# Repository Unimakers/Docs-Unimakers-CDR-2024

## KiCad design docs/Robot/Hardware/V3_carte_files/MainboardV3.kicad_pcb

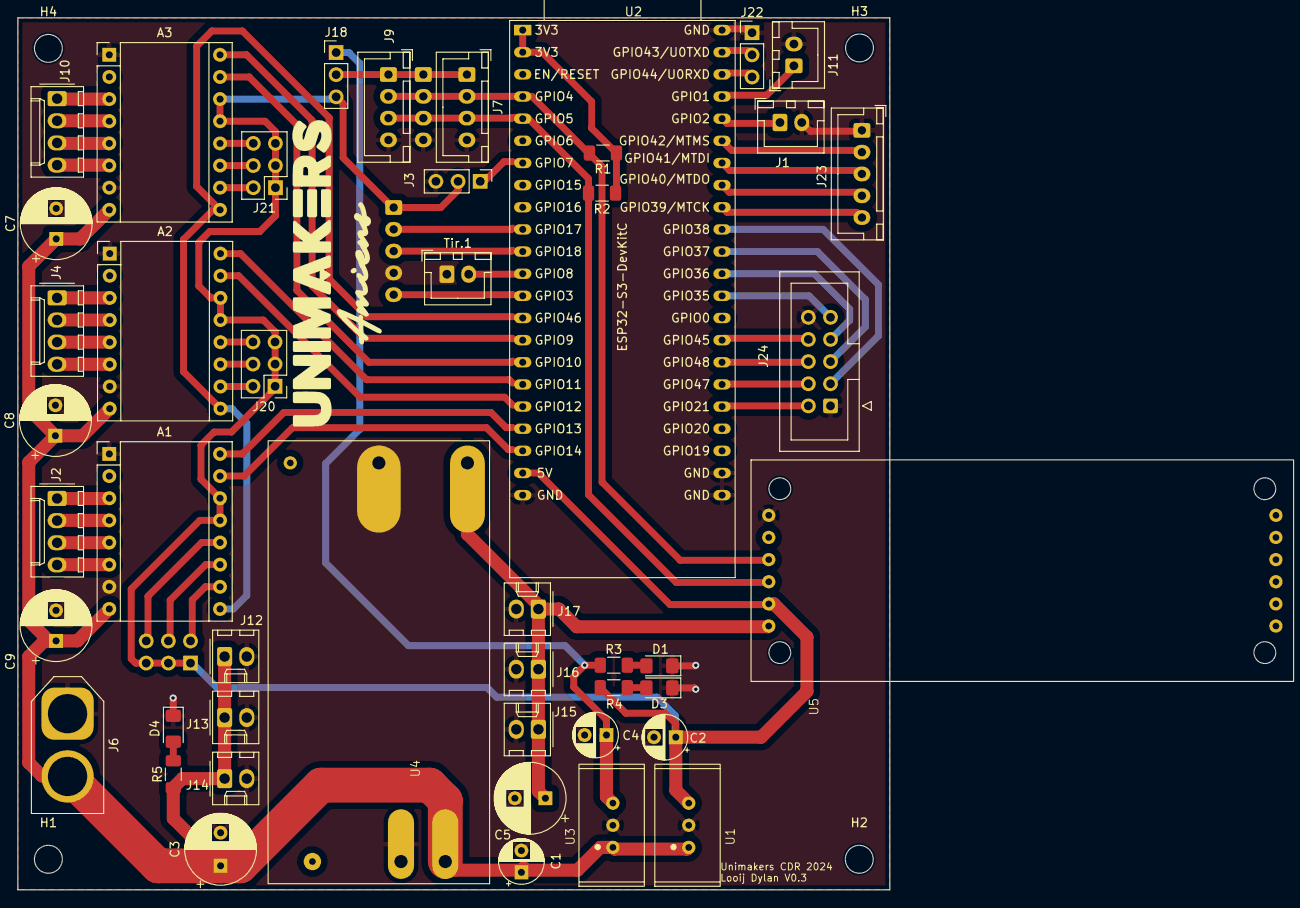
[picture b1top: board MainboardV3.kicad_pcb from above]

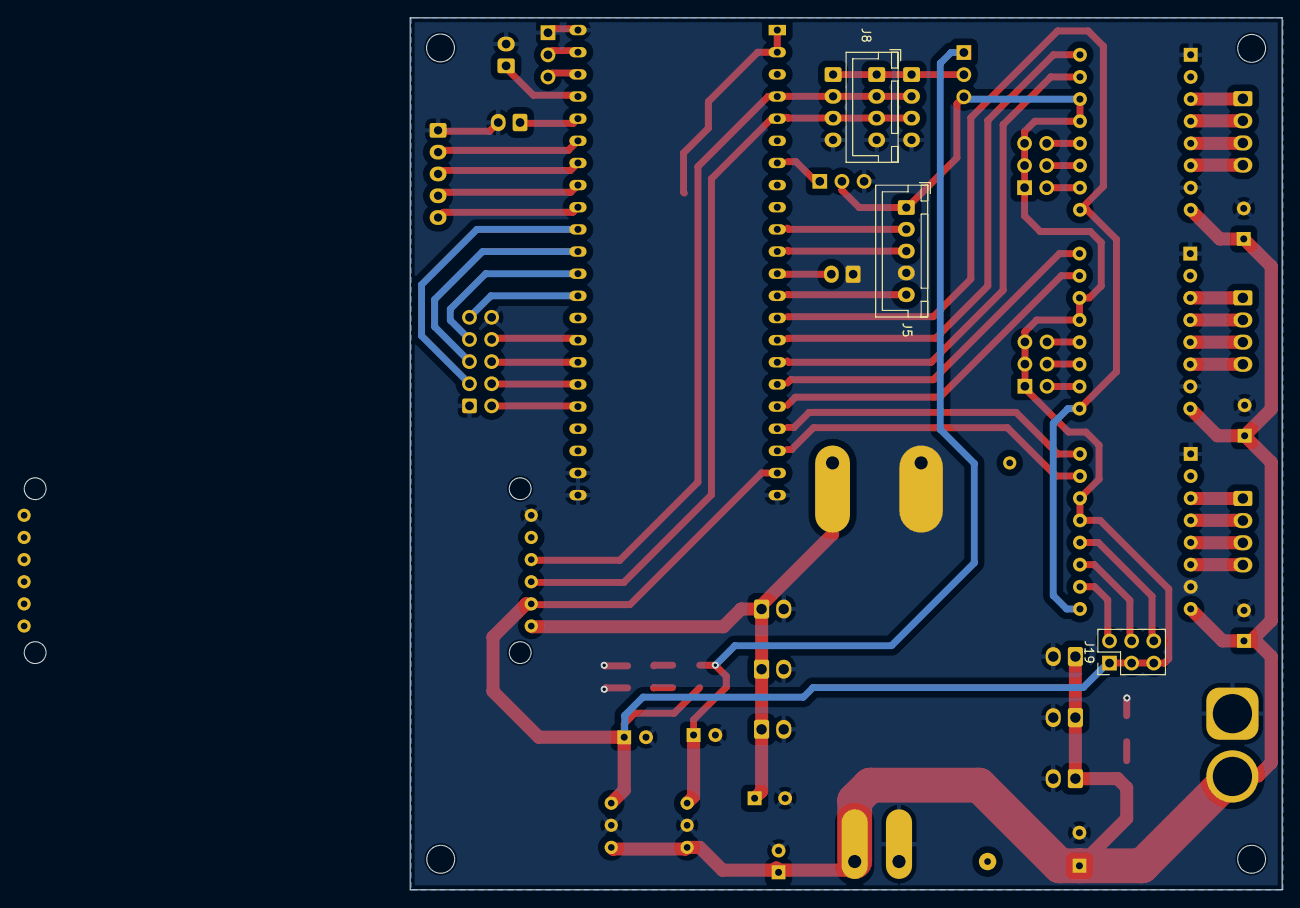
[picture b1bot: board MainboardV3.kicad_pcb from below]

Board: 2 copper layers, 100.0 x 100.0 mm, 53 parts (3 on the bottom side), 61 nets.

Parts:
A1, A2, A3: Pololu_Breakout_DRV8825; Pololu_Breakout-16_15.2x20.3mm
C1, C2, C4: C_Polarized; CP_Radial_D5.0mm_P2.50mm
C3: C_Polarized; CP_Radial_D8.0mm_P3.80mm
C5, C7, C8, C9: C_Polarized; CP_Radial_D8.0mm_P3.50mm
D1, D3, D4: LED_Small; LED_1206_3216Metric_Pad1.42x1.75mm_HandSolder
H1, H2, H3, H4: MountingHole; MountingHole_3.2mm_M3
J1, J11: Conn_01x02; JST_XH_B2B-XH-A_1x02_P2.50mm_Vertical
J2, J4, J10: Conn_01x04; Molex_KK-254_AE-6410-04A_1x04_P2.54mm_Vertical
J3, J18, J22: Conn_01x03; PinHeader_1x03_P2.54mm_Vertical
J5, J23: Conn_01x05; JST_XH_B5B-XH-A_1x05_P2.50mm_Vertical
J6: Conn_01x02; AMASS_XT60-M_1x02_P7.20mm_Vertical
J7, J8, J9: Conn_01x04; JST_XH_B4B-XH-A_1x04_P2.50mm_Vertical
J12, J13, J14, J15, J16, J17: Conn_01x02; Molex_KK-254_AE-6410-02A_1x02_P2.54mm_Vertical
J19, J20, J21: Conn_02x03_Odd_Even; PinHeader_2x03_P2.54mm_Vertical
J24: Conn_02x05_Odd_Even; IDC-Header_2x05_P2.54mm_Vertical
R1, R2: R; R_1206_3216Metric_Pad1.30x1.75mm_HandSolder
R3, R4, R5: R_Small; R_1206_3216Metric_Pad1.30x1.75mm_HandSolder
Tir.1: Conn_01x02; JST_XH_B2B-XH-A_1x02_P2.50mm_Vertical
U1: TSR_2-2450; Traco 2- 24xx
U2: ESP32-S3-DevKitC
U3: TSR_2-2433; Traco 2- 24xx
U4: TEN_50-2411WI; Traco TEN 50 series
U5: PCA9685breakout

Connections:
+3.3V: R1.1, R2.1, U2.1 (3V3), U2.2 (3V3)
+3.3VP: C4.1, J18.1, R3.1, U3.3 (VO)
+5V: A1.13 (~RST), A1.14 (~SLP), A2.13 (~RST), A2.14 (~SLP), A3.13 (~RST), A3.14 (~SLP), C2.1, J3.2, J5.1, J18.3, J19.1, J19.3, J19.5, J20.1, J20.3, J20.5, J21.1, J21.3, J21.5, R4.1, U1.3 (VO), U2.21 (5V), U5.4 (VCC)
+5VP: C5.1, J15.1, J16.1, J17.1, U4.4 (+Vout), U5.5 (V+_6VMax)
+12V: A1.8 (VMOT), A2.8 (VMOT), A3.8 (VMOT), C1.1, C3.1, C7.1, C8.1, C9.1, J6.2, J12.1, J13.1, J14.1, R5.1, U1.1 (VI), U3.1 (VI), U4.1 (+Vin)
/GP1: J11.1, U2.41 (GPIO1/ADC1_CH0)
/GP2: J1.1, U2.40 (GPIO2/ADC1_CH1)
DIR1: A1.16 (DIR), U2.19 (GPIO13/ADC2_CH2)
DIR2: A2.16 (DIR), U2.17 (GPIO11/ADC2_CH0)
DIR3: A3.16 (DIR), U2.15 (GPIO9/ADC1_CH8)
EN: A1.9 (~EN), A2.9 (~EN), A3.9 (~EN), U2.14 (GPIO46)
GND: A1.1 (GND), A1.7 (GND), A2.1 (GND), A2.7 (GND), A3.1 (GND), A3.7 (GND), C1.2, C2.2, C3.2, C4.2, C5.2, C7.2, C8.2, C9.2, D1.1 (K), D3.1 (K), D4.1 (K), J1.2, J3.3, J5.4, J6.1, J7.4, J8.4, J9.4, J11.2, J12.2, J13.2, J14.2, J15.2, J16.2, J17.2, J22.1, J23.1, J24.1, J24.10, Tir.1.1, U1.2 (GND), U2.22 (GND), U2.23 (GND), U2.24 (GND), U2.44 (GND), U3.2 (GND), U4.2 (-Vin), U4.5 (-Vout), U5.0 (GND)
GPI035: J24.9, U2.32 (GPIO35)
GPIO21: J24.2, U2.27 (GPIO21)
GPIO36: J24.7, U2.33 (GPIO36)
GPIO37: J24.5, U2.34 (GPIO37)
GPIO38: J24.3, U2.35 (GPIO38)
GPIO45: J24.8, U2.30 (GPIO45)
GPIO47: J24.4, U2.28 (GPIO47)
GPIO48: J24.6, U2.29 (GPIO48)
LIDARRX: J5.2, U2.10 (GPIO17/ADC2_CH6)
LIDARTX: J5.3, U2.11 (GPIO18/ADC2_CH7)
Neopixel: J3.1, U2.7 (GPIO7/ADC1_CH6)
unnamed: A1.4 (A1), J2.2
unnamed: A1.3 (A2), J2.1
unnamed: A1.5 (B1), J2.3
unnamed: A1.6 (B2), J2.4
unnamed: A1.10 (M0), J19.2
unnamed: A1.11 (M1), J19.4
unnamed: A1.12 (M2), J19.6
unnamed: A2.4 (A1), J4.2
unnamed: A2.3 (A2), J4.1
unnamed: A2.5 (B1), J4.3
unnamed: A2.6 (B2), J4.4
unnamed: A2.10 (M0), J20.2
unnamed: A2.11 (M1), J20.4
unnamed: A2.12 (M2), J20.6
unnamed: A3.4 (A1), J10.2
unnamed: A3.3 (A2), J10.1
unnamed: A3.5 (B1), J10.3
unnamed: A3.6 (B2), J10.4
unnamed: A3.10 (M0), J21.2
unnamed: A3.11 (M1), J21.4
unnamed: A3.12 (M2), J21.6
unnamed: D1.2 (A), R3.2
unnamed: D3.2 (A), R4.2
unnamed: D4.2 (A), R5.2
unnamed: J7.1, J8.1, J9.1, J18.2
unnamed: J22.2, U2.43 (GPIO43/U0TXD)
unnamed: J22.3, U2.42 (GPIO44/U0RXD)
unnamed: J23.2, U2.39 (GPIO42/MTMS)
unnamed: J23.3, U2.38 (GPIO41/MTDI)
unnamed: J23.4, U2.37 (GPIO40/MTDO)
unnamed: J23.5, U2.36 (GPIO39/MTCK)
unnamed: Tir.1.2, U2.12 (GPIO8/ADC1_CH7)
PWMLIDAR: J5.5, U2.13 (GPIO3/ADC1_CH2)
SCL: J7.2, J8.2, J9.2, R1.2, U2.4 (GPIO4/ADC1_CH3), U5.2 (SCL)
SDA: J7.3, J8.3, J9.3, R2.2, U2.5 (GPIO5/ADC1_CH4), U5.3 (SDA)
STEP1: A1.15 (STEP), U2.20 (GPIO14/ADC2_CH3)
STEP2: A2.15 (STEP), U2.18 (GPIO12/ADC2_CH1)
STEP3: A3.15 (STEP), U2.16 (GPIO10/ADC1_CH9)

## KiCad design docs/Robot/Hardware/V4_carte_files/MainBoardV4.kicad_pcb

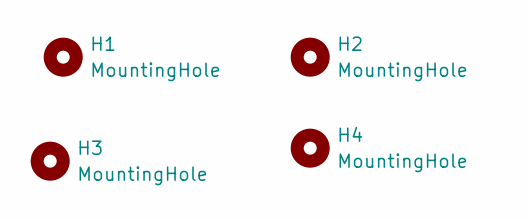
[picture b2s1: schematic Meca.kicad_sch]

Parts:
H1, H2, H3, H4: MountingHole; MountingHole_3.2mm_M3

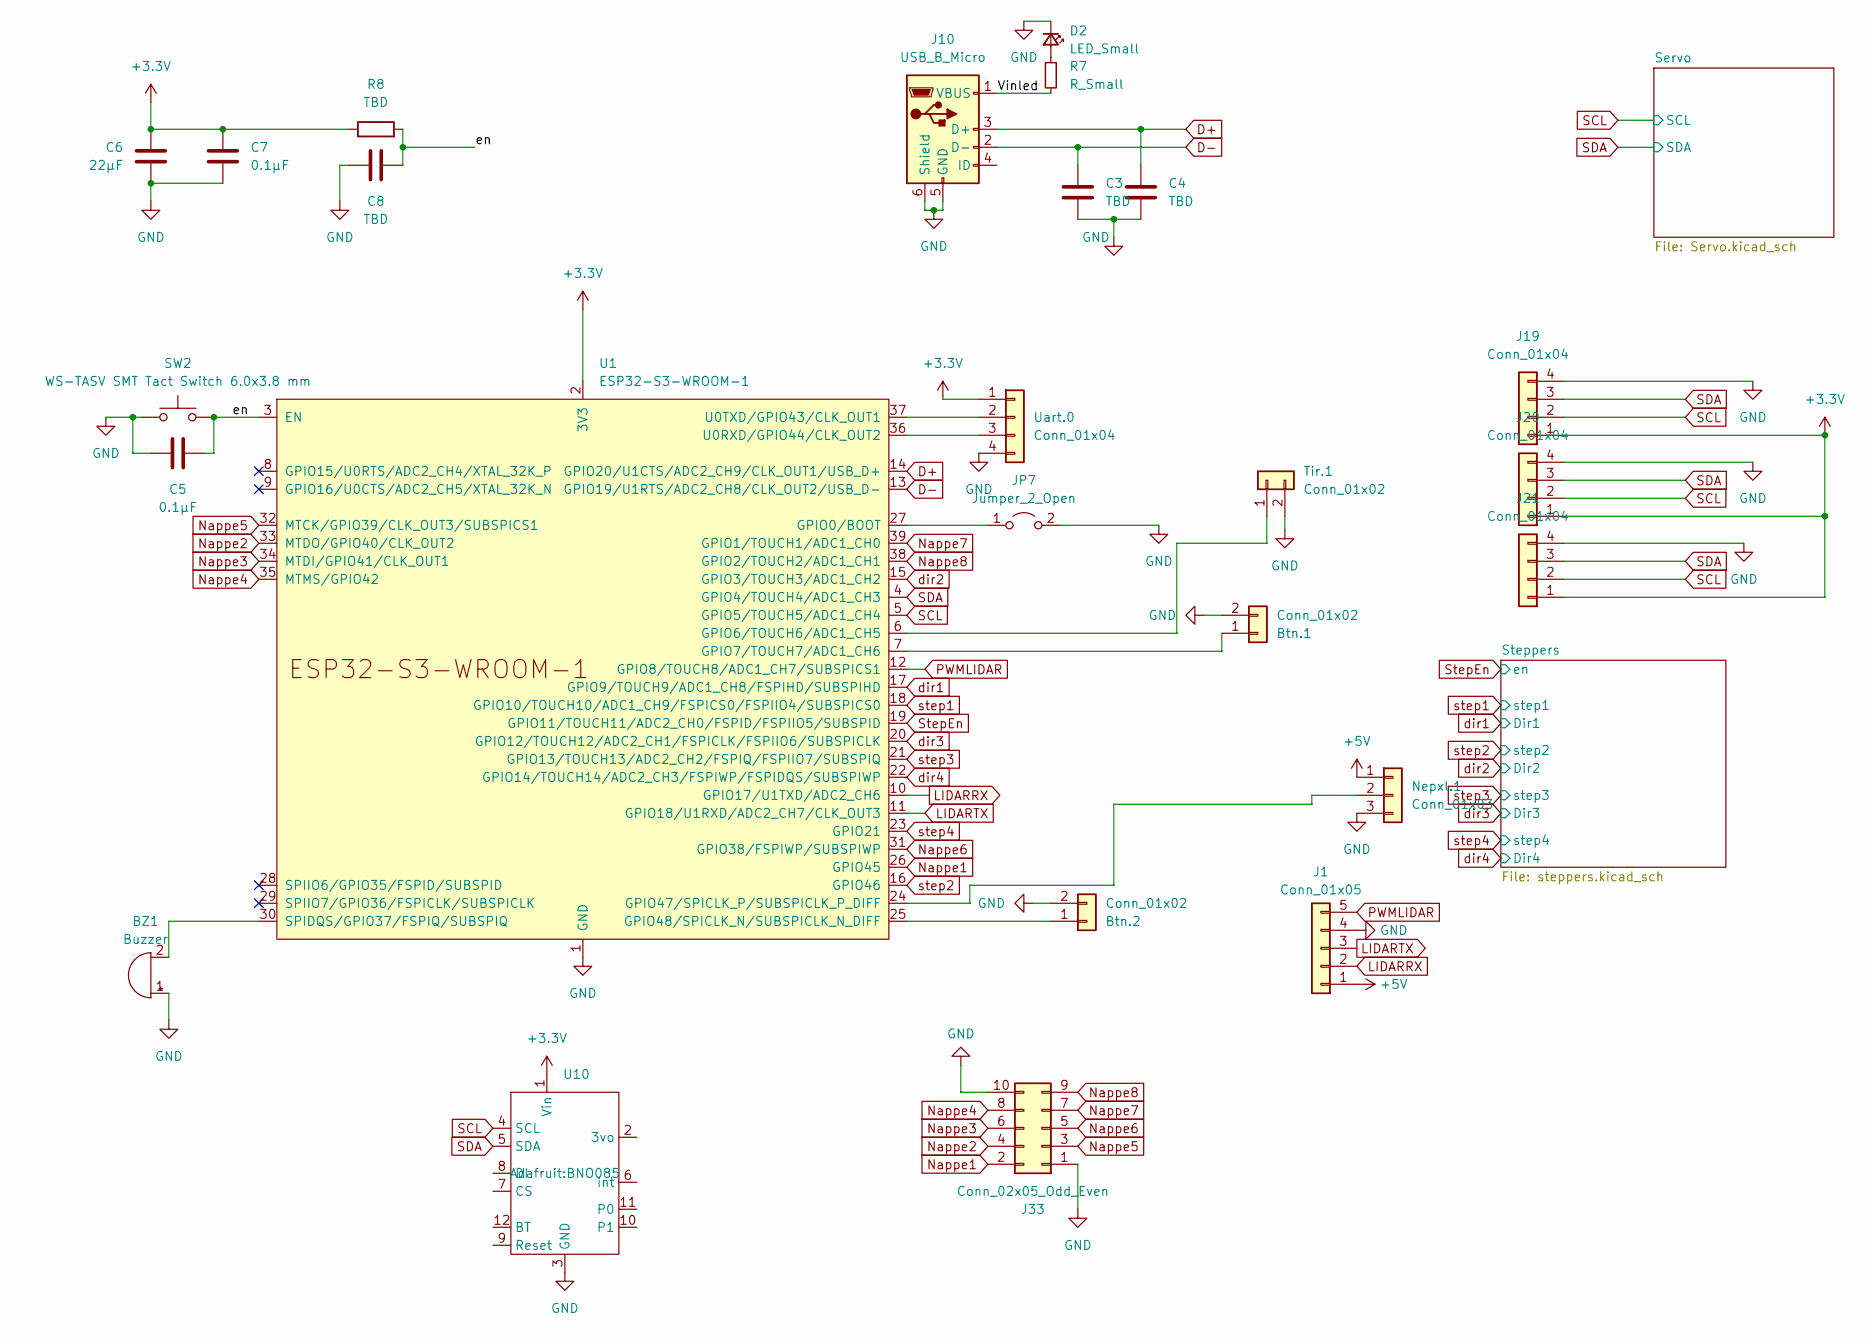
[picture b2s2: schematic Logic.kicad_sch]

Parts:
BZ1: Buzzer; Buzzer_12x9.5RM7.6
Btn.1, Btn.2: Conn_01x02; JST_XH_B2B-XH-A_1x02_P2.50mm_Vertical
C3, C4, C8: TBD; C_0805_2012Metric_Pad1.18x1.45mm_HandSolder
C5, C7: 0.1µF; C_0805_2012Metric_Pad1.18x1.45mm_HandSolder
C6: 22µF; C_0805_2012Metric_Pad1.18x1.45mm_HandSolder
D2: LED_Small; LED_1206_3216Metric_Pad1.42x1.75mm_HandSolder
J1: Conn_01x05; JST_XH_B5B-XH-A_1x05_P2.50mm_Vertical
J10: USB_B_Micro; USB_Micro-B_Wuerth_629105150521
J19, J20, J21: Conn_01x04; JST_XH_B4B-XH-A_1x04_P2.50mm_Vertical
J33: Conn_02x05_Odd_Even; IDC-Header_2x05_P2.54mm_Vertical
JP7: Jumper_2_Open; PinHeader_1x02_P2.54mm_Vertical
Nepxl.1: Conn_01x03; PinSocket_1x03_P2.54mm_Vertical
R7: R_Small; R_1206_3216Metric_Pad1.30x1.75mm_HandSolder
R8: TBD; R_1206_3216Metric_Pad1.30x1.75mm_HandSolder
SW2: WS-TASV SMT Tact Switch 6.0x3.8 mm; WS-TASV SMT Tact Switch
Tir.1: Conn_01x02; JST_XH_B2B-XH-A_1x02_P2.50mm_Vertical
U1: ESP32-S3-WROOM-1
U10: BNO085
Uart.0: Conn_01x04; JST_XH_B4B-XH-A_1x04_P2.50mm_Vertical

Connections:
+3.3V: C6.2, C7.2, J19.1, J20.1, J21.1, R8.1, U1.2 (3V3), U10.1 (Vin), Uart.0.1; also elsewhere on the board
+5V: J1.1, Nepxl.1.1; also elsewhere on the board
/Logic/Vinled: J10.1 (VBUS), R7.2
/Logic/en: C5.2, C8.1, R8.2, SW2.2, U1.3 (EN)
D+: C4.1, J10.3 (D+), U1.14 (GPIO20/U1CTS/ADC2_CH9/CLK_OUT1/USB_D+)
D-: C3.1, J10.2 (D-), U1.13 (GPIO19/U1RTS/ADC2_CH8/CLK_OUT2/USB_D-)
GND: BZ1.1 (-), Btn.1.2, Btn.2.2, C3.2, C4.2, C5.1, C6.1, C7.1, C8.2, D2.1 (K), J1.4, J10.5 (GND), J10.6 (Shield), J19.4, J20.4, J21.4, J33.1, J33.10, JP7.2 (B), Nepxl.1.3, SW2.1, Tir.1.2, U1.1 (GND), U1.40 (GND), U1.41 (GND), U10.3 (GND), Uart.0.4; also elsewhere on the board
LIDARRX: J1.2, U1.10 (GPIO17/U1TXD/ADC2_CH6)
LIDARTX: J1.3, U1.11 (GPIO18/U1RXD/ADC2_CH7/CLK_OUT3)
Nappe1: J33.2, U1.26 (GPIO45)
Nappe2: J33.4, U1.33 (MTDO/GPIO40/CLK_OUT2)
Nappe3: J33.6, U1.34 (MTDI/GPIO41/CLK_OUT1)
Nappe4: J33.8, U1.35 (MTMS/GPIO42)
Nappe5: J33.3, U1.32 (MTCK/GPIO39/CLK_OUT3/SUBSPICS1)
Nappe6: J33.5, U1.31 (GPIO38/FSPIWP/SUBSPIWP)
Nappe7: J33.7, U1.39 (GPIO1/TOUCH1/ADC1_CH0)
Nappe8: J33.9, U1.38 (GPIO2/TOUCH2/ADC1_CH1)
unnamed: BZ1.2 (+), U1.30 (SPIDQS/GPIO37/FSPIQ/SUBSPIQ)
unnamed: Btn.1.1, U1.7 (GPIO7/TOUCH7/ADC1_CH6)
unnamed: Btn.2.1, U1.25 (GPIO48/SPICLK_N/SUBSPICLK_N_DIFF)
unnamed: D2.2 (A), R7.1
unnamed: JP7.1 (A), U1.27 (GPIO0/BOOT)
unnamed: Nepxl.1.2, U1.24 (GPIO47/SPICLK_P/SUBSPICLK_P_DIFF)
unnamed: Tir.1.1, U1.6 (GPIO6/TOUCH6/ADC1_CH5)
unnamed: U1.36 (U0RXD/GPIO44/CLK_OUT2), Uart.0.3
unnamed: U1.37 (U0TXD/GPIO43/CLK_OUT1), Uart.0.2
PWMLIDAR: J1.5, U1.12 (GPIO8/TOUCH8/ADC1_CH7/SUBSPICS1)
SCL: J19.2, J20.2, J21.2, U1.5 (GPIO5/TOUCH5/ADC1_CH4), U10.4 (SCL); also elsewhere on the board
SDA: J19.3, J20.3, J21.3, U1.4 (GPIO4/TOUCH4/ADC1_CH3), U10.5 (SDA); also elsewhere on the board
StepEn: U1.19 (GPIO11/TOUCH11/ADC2_CH0/FSPID/FSPIIO5/S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); also elsewhere on the board
dir1: U1.17 (GPIO9/TOUCH9/ADC1_CH8/FSPIHD/SUBSPIHD); also elsewhere on the board
dir2: U1.15 (GPIO3/TOUCH3/ADC1_CH2); also elsewhere on the board
dir3: U1.20 (GPIO12/TOUCH12/ADC2_CH1/FSPICLK/FSPIIO6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); also elsewhere on the board
dir4: U1.22 (GPIO14/TOUCH14/ADC2_CH3/FSPIWP/FSPIDQS/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); also elsewhere on the board
step1: U1.18 (GPIO10/TOUCH10/ADC1_CH9/FSPICS0/FSPIIO4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); also elsewhere on the board
step2: U1.16 (GPIO46); also elsewhere on the board
step3: U1.21 (GPIO13/TOUCH13/ADC2_CH2/FSPIQ/FSPIIO7/S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); also elsewhere on the board
step4: U1.23 (GPIO21); also elsewhere on the board

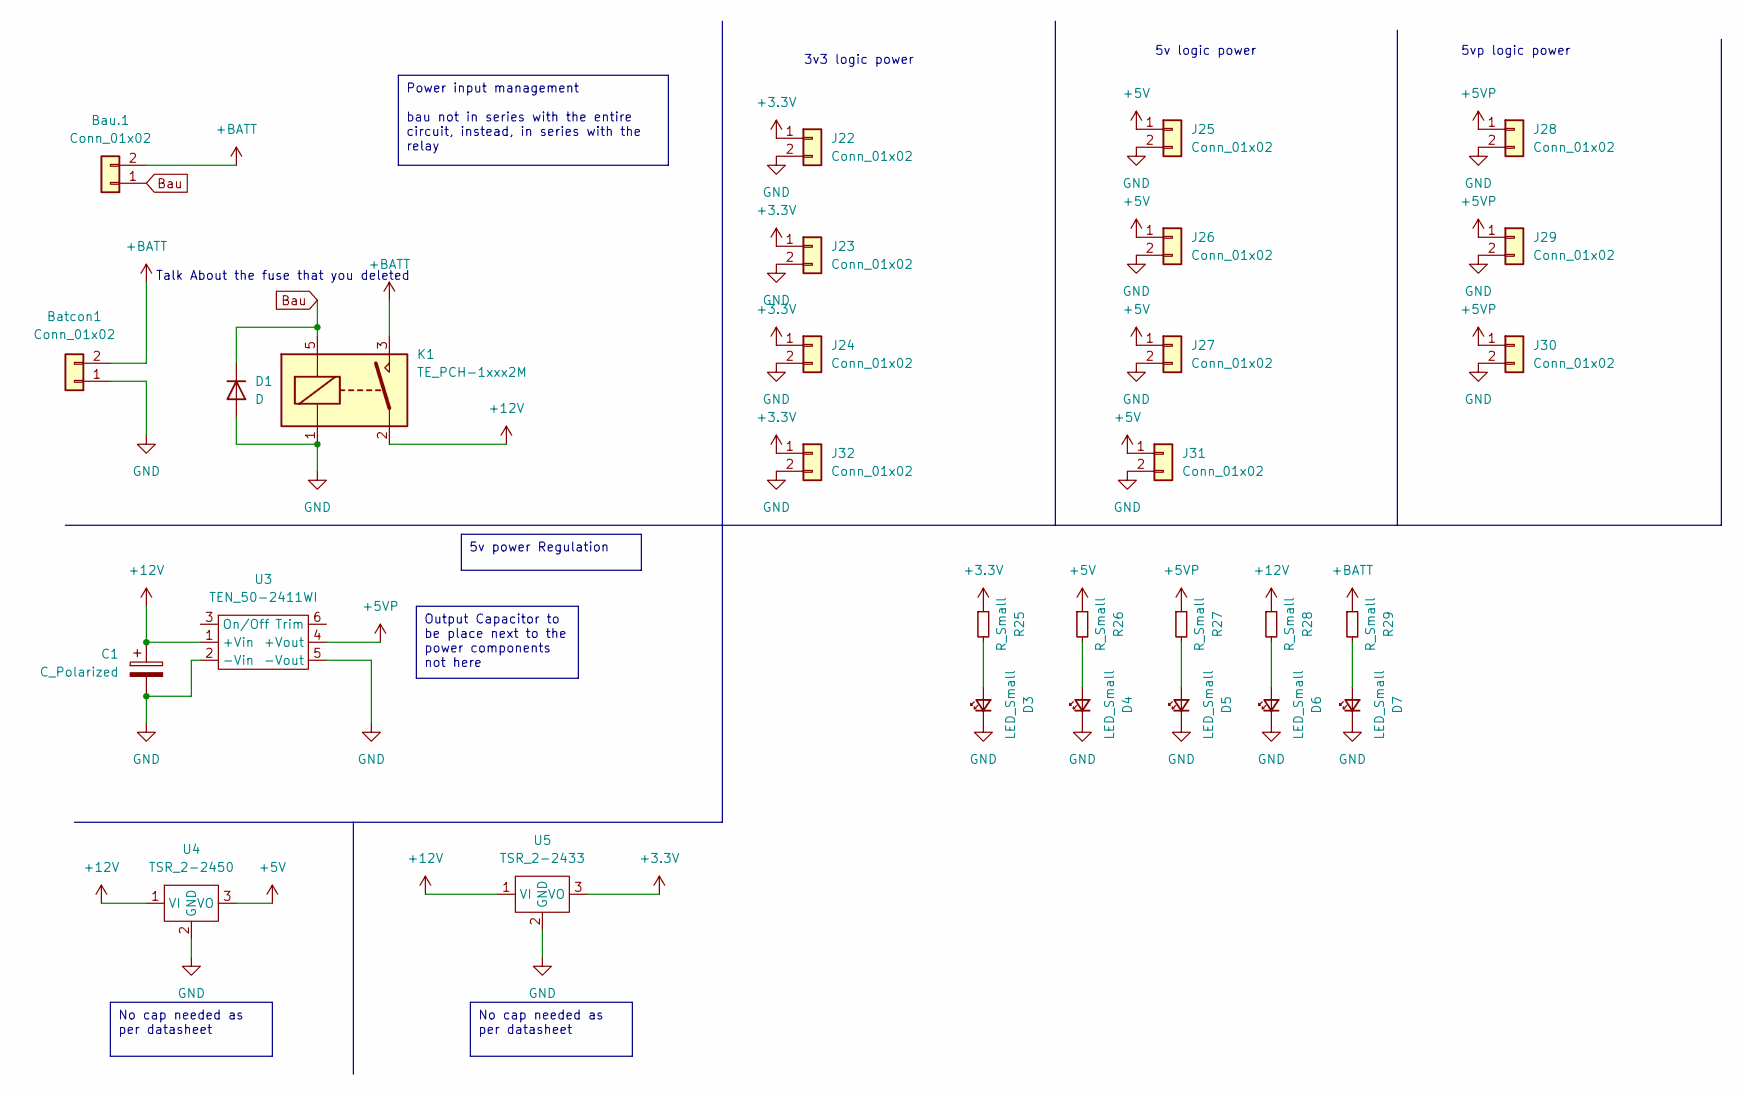
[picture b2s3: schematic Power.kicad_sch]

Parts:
Batcon1: Conn_01x02; AMASS_XT60-F_1x02_P7.20mm_Vertical
Bau.1: Conn_01x02; Molex_KK-254_AE-6410-02A_1x02_P2.54mm_Vertical
C1: C_Polarized
D1: D; D_DO-35_SOD27_P10.16mm_Horizontal
D3, D4, D5, D6, D7: LED_Small; LED_1206_3216Metric_Pad1.42x1.75mm_HandSolder
J22, J23, J24, J25, J26, J27, J28, J29, J30, J31, J32: Conn_01x02; Molex_KK-254_AE-6410-02A_1x02_P2.54mm_Vertical
K1: TE_PCH-1xxx2M; Relay_SPST_TE_PCH-1xxx2M
R25, R26, R27, R28, R29: R_Small; LED_1206_3216Metric_Pad1.42x1.75mm_HandSolder
U3: TEN_50-2411WI; Traco TEN 50 series
U4: TSR_2-2450; Traco 2- 24xx
U5: TSR_2-2433; Traco 2- 24xx

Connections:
+3.3V: J22.1, J23.1, J24.1, J32.1, R25.1, U5.3 (VO); also elsewhere on the board
+5V: J25.1, J26.1, J27.1, J31.1, R26.1, U4.3 (VO); also elsewhere on the board
+5VP: J28.1, J29.1, J30.1, R27.1, U3.4 (+Vout); also elsewhere on the board
+12V: C1.1, K1.2, R28.1, U3.1 (+Vin), U4.1 (VI), U5.1 (VI); also elsewhere on the board
+BATT: Batcon1.2, Bau.1.2, K1.3, R29.1
Bau: Bau.1.1, D1.1 (K), K1.5
GND: Batcon1.1, C1.2, D1.2 (A), D3.1 (K), D4.1 (K), D5.1 (K), D6.1 (K), D7.1 (K), J22.2, J23.2, J24.2, J25.2, J26.2, J27.2, J28.2, J29.2, J30.2, J31.2, J32.2, K1.1, U3.2 (-Vin), U3.5 (-Vout), U4.2 (GND), U5.2 (GND); also elsewhere on the board
unnamed: D3.2 (A), R25.2
unnamed: D4.2 (A), R26.2
unnamed: D5.2 (A), R27.2
unnamed: D6.2 (A), R28.2
unnamed: D7.2 (A), R29.2

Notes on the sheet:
Output Capacitor to be place next to the power components not here
5v power Regulation
No cap needed as per datasheet
Power input management bau not in series with the entire circuit, instead, in series with the relay
5vp logic power
Talk About the fuse that you deleted
5v logic power
3v3 logic power

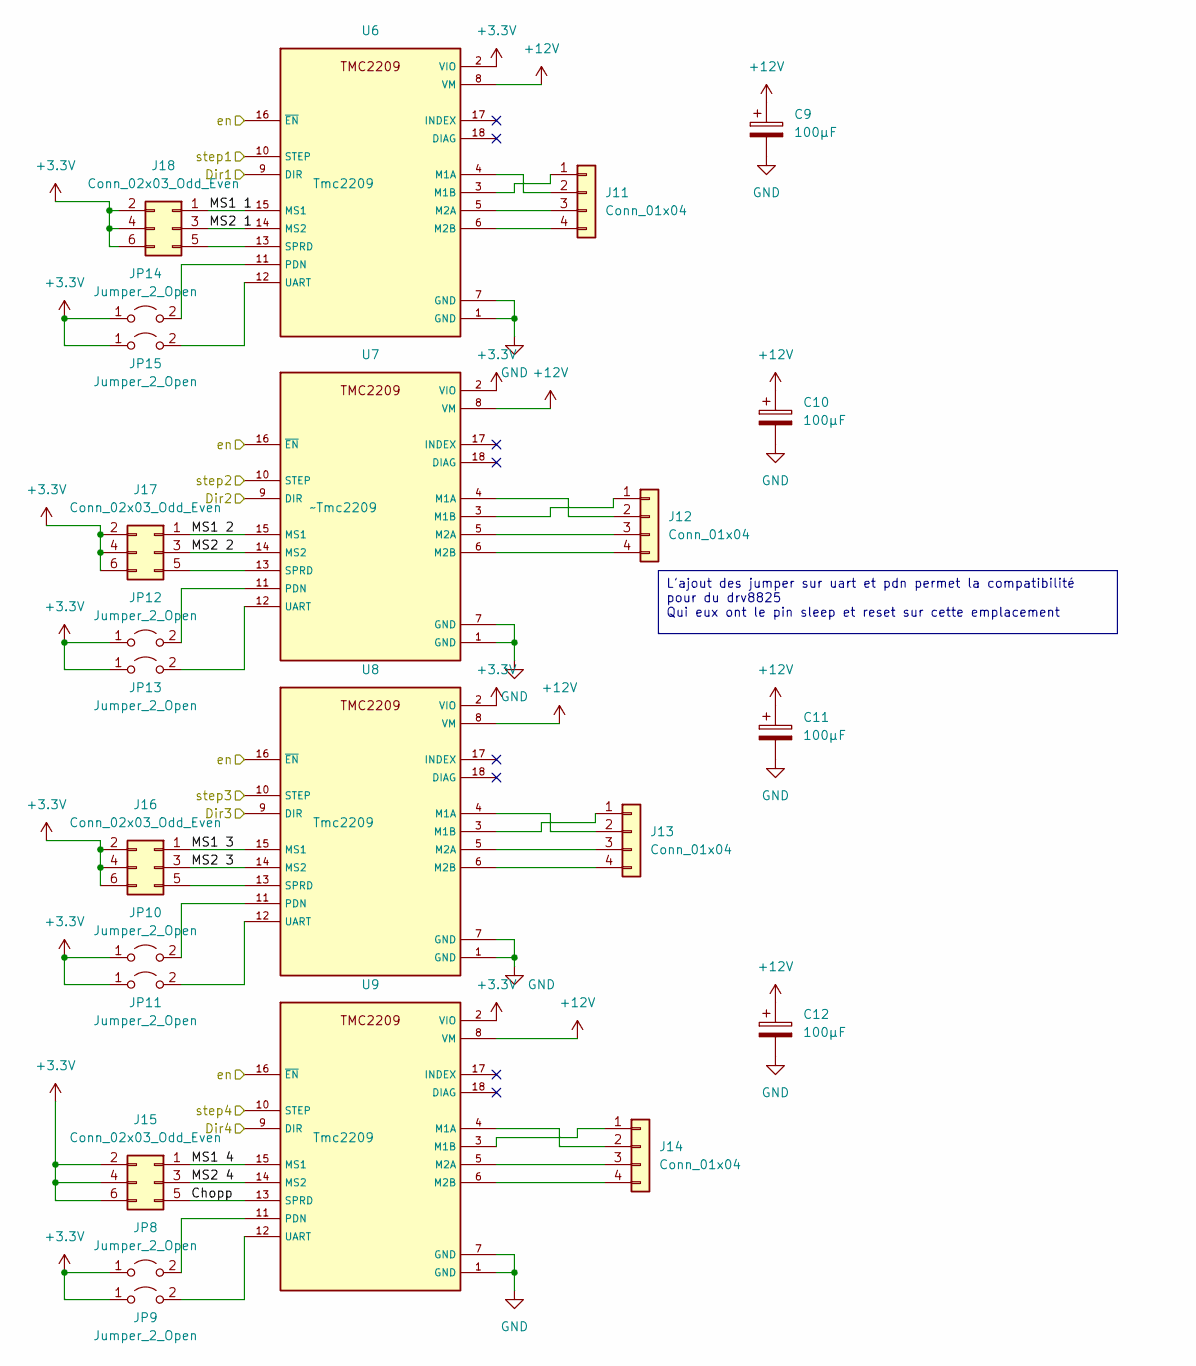
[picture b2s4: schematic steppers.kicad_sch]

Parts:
C9, C10, C11, C12: 100µF; CP_Elec_10x10.5
J11, J12, J13, J14: Conn_01x04; Molex_KK-254_AE-6410-04A_1x04_P2.54mm_Vertical
J15, J16, J17, J18: Conn_02x03_Odd_Even; PinHeader_2x03_P2.54mm_Vertical
JP8, JP9, JP10, JP11, JP12, JP13, JP14, JP15: Jumper_2_Open; SolderJumper-2_P1.3mm_Open_Pad1.0x1.5mm
U6, U8, U9: Tmc2209; BOB_TMC2209_SILENTSTEPSTICK
U7: ~Tmc2209; BOB_TMC2209_SILENTSTEPSTICK

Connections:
+3.3V: J15.2, J15.4, J15.6, J16.2, J16.4, J16.6, J17.2, J17.4, J17.6, J18.2, J18.4, J18.6, JP8.1 (A), JP9.1 (A), JP10.1 (A), JP11.1 (A), JP12.1 (A), JP13.1 (A), JP14.1 (A), JP15.1 (A), U6.2 (VIO), U7.2 (VIO), U8.2 (VIO), U9.2 (VIO); also elsewhere on the board
+12V: C9.1, C10.1, C11.1, C12.1, U6.8 (VM), U7.8 (VM), U8.8 (VM), U9.8 (VM); also elsewhere on the board
/Logic/Steppers/Chopp: J15.5, U9.13 (SPRD)
/Logic/Steppers/MS1 1: J18.1, U6.15 (MS1)
/Logic/Steppers/MS1 2: J17.1, U7.15 (MS1)
/Logic/Steppers/MS1 3: J16.1, U8.15 (MS1)
/Logic/Steppers/MS1 4: J15.1, U9.15 (MS1)
/Logic/Steppers/MS2 1: J18.3, U6.14 (MS2)
/Logic/Steppers/MS2 2: J17.3, U7.14 (MS2)
/Logic/Steppers/MS2 3: J16.3, U8.14 (MS2)
/Logic/Steppers/MS2 4: J15.3, U9.14 (MS2)
GND: C9.2, C10.2, C11.2, C12.2, U6.1 (GND), U6.7 (GND), U7.1 (GND), U7.7 (GND), U8.1 (GND), U8.7 (GND), U9.1 (GND), U9.7 (GND); also elsewhere on the board
unnamed: J11.1, U6.3 (M1B)
unnamed: J11.2, U6.4 (M1A)
unnamed: J11.3, U6.5 (M2A)
unnamed: J11.4, U6.6 (M2B)
unnamed: J12.1, U7.3 (M1B)
unnamed: J12.2, U7.4 (M1A)
unnamed: J12.3, U7.5 (M2A)
unnamed: J12.4, U7.6 (M2B)
unnamed: J13.1, U8.3 (M1B)
unnamed: J13.2, U8.4 (M1A)
unnamed: J13.3, U8.5 (M2A)
unnamed: J13.4, U8.6 (M2B)
unnamed: J14.1, U9.3 (M1B)
unnamed: J14.2, U9.4 (M1A)
unnamed: J14.3, U9.5 (M2A)
unnamed: J14.4, U9.6 (M2B)
unnamed: J16.5, U8.13 (SPRD)
unnamed: J17.5, U7.13 (SPRD)
unnamed: J18.5, U6.13 (SPRD)
unnamed: JP8.2 (B), U9.11 (PDN)
unnamed: JP9.2 (B), U9.12 (UART)
unnamed: JP10.2 (B), U8.11 (PDN)
unnamed: JP11.2 (B), U8.12 (UART)
unnamed: JP12.2 (B), U7.11 (PDN)
unnamed: JP13.2 (B), U7.12 (UART)
unnamed: JP14.2 (B), U6.11 (PDN)
unnamed: JP15.2 (B), U6.12 (UART)
StepEn: U6.16 (~EN), U7.16 (~EN), U8.16 (~EN), U9.16 (~EN); also elsewhere on the board
dir1: U6.9 (DIR); also elsewhere on the board
dir2: U7.9 (DIR); also elsewhere on the board
dir3: U8.9 (DIR); also elsewhere on the board
dir4: U9.9 (DIR); also elsewhere on the board
step1: U6.10 (STEP); also elsewhere on the board
step2: U7.10 (STEP); also elsewhere on the board
step3: U8.10 (STEP); also elsewhere on the board
step4: U9.10 (STEP); also elsewhere on the board

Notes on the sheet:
L'ajout des jumper sur uart et pdn permet la compatibilité pour du drv8825 Qui eux ont le pin sleep et reset sur cette emplacement

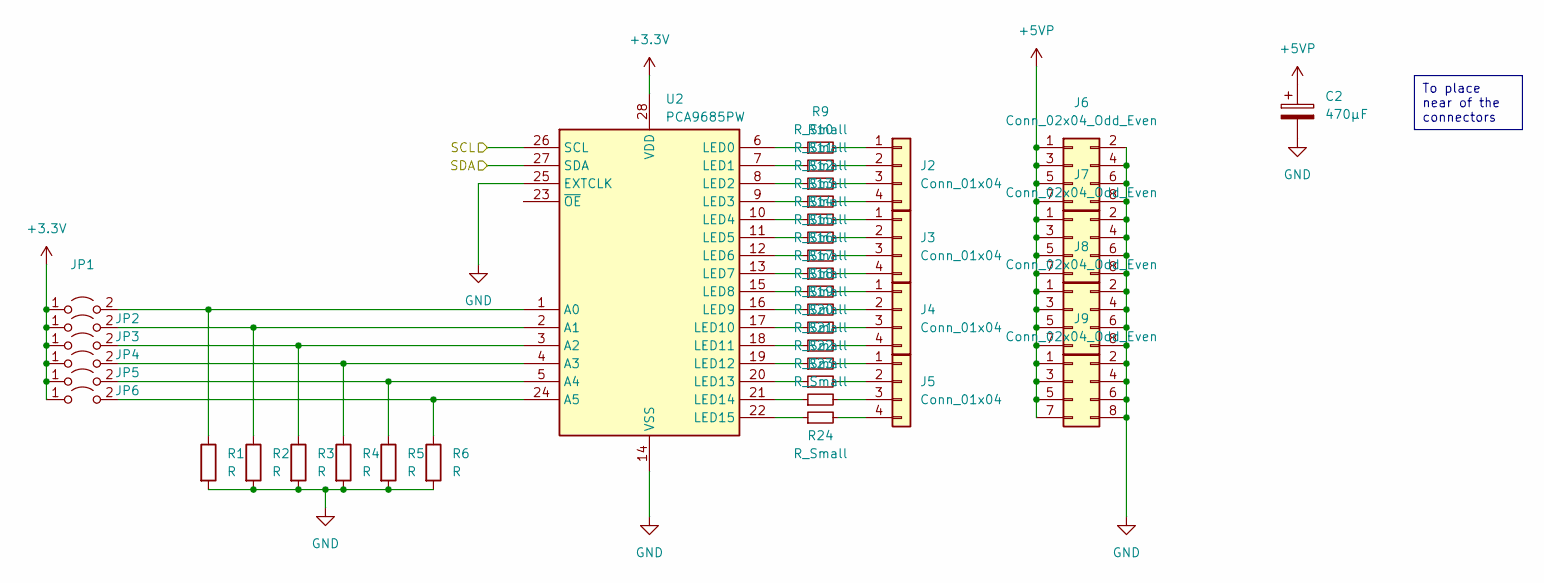
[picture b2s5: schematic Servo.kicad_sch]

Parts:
C2: 470µF; CP_Elec_10x10.5
J2, J3, J4, J5: Conn_01x04; PinHeader_1x04_P2.54mm_Vertical
J6, J7, J8, J9: Conn_02x04_Odd_Even; PinHeader_2x04_P2.54mm_Vertical
JP1, JP2, JP3, JP4, JP5, JP6: Jumper_2_Open; SolderJumper-2_P1.3mm_Open_Pad1.0x1.5mm
R1, R2, R3, R4, R5, R6: R; R_1206_3216Metric_Pad1.30x1.75mm_HandSolder
R9, R10, R11, R12, R13, R14, R15, R16, R17, R18, R19, R20, R21, R22, R23, R24: R_Small; R_1206_3216Metric_Pad1.30x1.75mm_HandSolder
U2: PCA9685PW; TSSOP-28_4.4x9.7mm_P0.65mm

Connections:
+3.3V: JP1.1 (A), JP2.1 (A), JP3.1 (A), JP4.1 (A), JP5.1 (A), JP6.1 (A), U2.28 (VDD); also elsewhere on the board
+5VP: C2.1, J6.1, J6.3, J6.5, J6.7, J7.1, J7.3, J7.5, J7.7, J8.1, J8.3, J8.5, J8.7, J9.1, J9.3, J9.5, J9.7; also elsewhere on the board
GND: C2.2, J6.2, J6.4, J6.6, J6.8, J7.2, J7.4, J7.6, J7.8, J8.2, J8.4, J8.6, J8.8, J9.2, J9.4, J9.6, J9.8, R1.2, R2.2, R3.2, R4.2, R5.2, R6.2, U2.14 (VSS), U2.25 (EXTCLK); also elsewhere on the board
unnamed: J2.1, R9.2
unnamed: J2.2, R10.2
unnamed: J2.3, R11.2
unnamed: J2.4, R12.2
unnamed: J3.1, R13.2
unnamed: J3.2, R14.2
unnamed: J3.3, R15.2
unnamed: J3.4, R16.2
unnamed: J4.1, R17.2
unnamed: J4.2, R18.2
unnamed: J4.3, R19.2
unnamed: J4.4, R20.2
unnamed: J5.1, R21.2
unnamed: J5.2, R22.2
unnamed: J5.3, R23.2
unnamed: J5.4, R24.2
unnamed: JP1.2 (B), R1.1, U2.1 (A0)
unnamed: JP2.2 (B), R2.1, U2.2 (A1)
unnamed: JP3.2 (B), R3.1, U2.3 (A2)
unnamed: JP4.2 (B), R4.1, U2.4 (A3)
unnamed: JP5.2 (B), R5.1, U2.5 (A4)
unnamed: JP6.2 (B), R6.1, U2.24 (A5)
unnamed: R9.1, U2.6 (LED0)
unnamed: R10.1, U2.7 (LED1)
unnamed: R11.1, U2.8 (LED2)
unnamed: R12.1, U2.9 (LED3)
unnamed: R13.1, U2.10 (LED4)
unnamed: R14.1, U2.11 (LED5)
unnamed: R15.1, U2.12 (LED6)
unnamed: R16.1, U2.13 (LED7)
unnamed: R17.1, U2.15 (LED8)
unnamed: R18.1, U2.16 (LED9)
unnamed: R19.1, U2.17 (LED10)
unnamed: R20.1, U2.18 (LED11)
unnamed: R21.1, U2.19 (LED12)
unnamed: R22.1, U2.20 (LED13)
unnamed: R23.1, U2.21 (LED14)
unnamed: R24.1, U2.22 (LED15)
SCL: U2.26 (SCL); also elsewhere on the board
SDA: U2.27 (SDA); also elsewhere on the board

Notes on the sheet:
To place near of the connectors

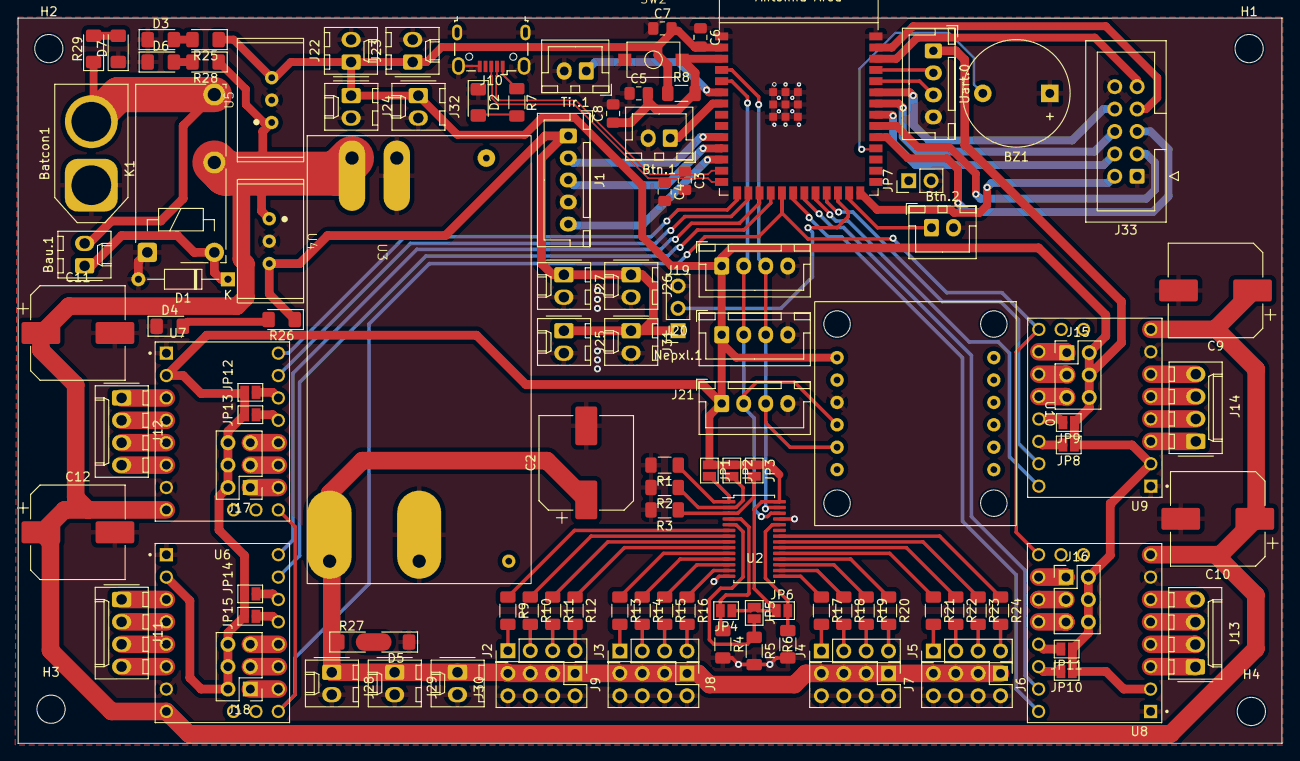
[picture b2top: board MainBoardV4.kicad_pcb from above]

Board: 2 copper layers, 143.3 x 82.3 mm, 119 parts (0 on the bottom side), 121 nets.

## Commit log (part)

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2024-01-31 TEST_julien
2024-01-31 Add Simulateur
2024-01-31 Ajout video
2024-01-31 Modif index
2024-02-01 Update Disposition
2024-02-01 Ajout Prog Robot
2024-02-11 Ajout Possibilité 3D
2024-02-12 Update hardware
2024-02-12 Mise a jour Hardware
2024-02-21 Ajout Visioneur Kicad
2024-02-27 Ajout du texte sur la pince, il manque encore les illustrations
2024-03-06 modif site partie simulateur
2024-03-06 modif
2024-03-08 modif simulateur 08/03/2024
2024-03-08 Fix js link
2024-03-08 Try fix link js
2024-03-08 Another fix?
2024-03-08 plz link Js
2024-03-08 Plz i'm desperate
2024-03-08 Link typo fix
2024-03-11 MAJ V1 carte
2024-03-11 Add V2 carte + bug fix
2024-03-11 Add pcb
2024-03-11 fix double kicanvas
2024-03-11 Maj V2 carte
2024-03-11 typo
2024-03-23 Enlévement des pages inutiles
2024-03-23 Rajout des 2 dernieres Cartes
2024-03-23 Bug fixes
2024-03-23 Ajout d'un page de réseaux avec post du projet uniquement
2024-03-23 fix some typos
2024-03-27 init programmation_pamis
    Création du fichier markdown et écriture en partie de l'introduction
2024-03-27 Add files via upload
    ajout du vinyle pour le simulateur de stratégie
2024-03-27 rangement des fichiers
2024-03-27 ajout mise en page
2024-03-31 ajout de la première partie du générateur de strategie
2024-03-31 ajout organisation pages
2024-04-01 Mise a jour Carte V1
2024-04-02 modif du nom
2024-04-02 modif ordre des pages
2024-04-02 modification des liens de p5.js et de p5.gui.js
2024-04-02 suppresion d'une variable
2024-04-02 suppresion des /blob/main
2024-04-02 Logique fonctionnelle incoming
2024-04-02 ajout fonction pour dessiner le terrain
2024-04-02 MaJ Documentation technique PCB PAMI
2024-04-04 Update and rename sketch.js to sketch.V_1.js and add all function
2024-04-04 modification de la source de mon fichier
2024-04-05 modif coordonées des points / ajout code sketch v2
2024-04-05 changement adresse fichiers
2024-04-05 test avec code de adrien
2024-04-05 modif des liens
2024-04-05 modif totale
2024-04-05 modif liens générateur
2024-04-05 ajout des fichiers de calcul de coordonées
2024-04-05 modif des includes
2024-04-05 sup de quelques boutons
2024-04-05 sup du delete mode
2024-04-05 modif du lien poi.h
2024-04-05 modif bordure et autres
2024-04-05 remaniement de la hierarchie des pages
2024-04-06 Modification partie mécanique
2024-05-17 Update La_mecanique.md
    explication holonome/différentiel
2024-05-23 add: algorigramme PAMI v1
2024-05-23 add: logique fonctionnelle
2024-05-23 Modification indec et objectifs
2024-05-23 space
2024-05-23 Maj Objectifs
2024-05-23 Bug fix
2024-05-23 add: début IDE
2024-05-23 Mise a jour poster
2024-05-23 Bug contournement github
2024-05-23 Fix jpg to png
2024-05-23 Fix?
2024-05-23 test
2024-05-23 add: more things
2024-05-23 Image centrée
2024-05-23 MAJ Actualité
2024-05-23 rmv doublon
2024-05-23 add children
2024-05-23 PDF add
2024-05-24 change: PAMI nav
2024-05-24 change: électronique name
2024-05-24 upload photo robot
2024-05-24 crea conception
2024-05-24 Create La_conception_du_chassis
2024-05-24 souite
2024-05-24 fix: oublie librairie
2024-05-24 [ci skip]
2024-05-24 Avancement doc conception
2024-05-24 smol fix
2024-05-24 proute
2024-05-24 Ajout d'image
2024-05-24 test liens
2024-05-24 photo ?
2024-05-24 Update La_conception_du_chassis
2024-05-24 add PAMI-V1
2024-05-24 Update navigation
2024-05-24 Rename La_conception_du_chassis to La_conception_du_chassis.md
2024-05-24 refactor
2024-05-24 Maybe
2024-05-24 Fix l'image qui se trouve là où elle doit pas être
2024-05-24 Create Carte_PAMI
2024-05-24 Update Carte_PAMI
2024-05-24 Update La_conception_du_chassis.md-transmission
2024-05-24 add: page Obstacles
2024-05-24 Create PCB_V1
2024-05-24 change: img
2024-05-24 fix La_conception_du_chassis.md
2024-05-24 test photo
2024-05-24 Ajouts des photo du robot
2024-05-24 new: blabla Obstacles
2024-05-24 new: Pollenisation
2024-05-25 creat 3d places
2024-05-25 test 3d
2024-05-25 again
2024-05-25 test again
2024-05-25 now it works
2024-05-25 clarification
2024-05-25 mise au claire
2024-05-25 change: steppers PAMI and things
2024-05-25 reparation fichier 1&2&3
2024-05-25 fix ?
2024-05-25 bug test
2024-05-25 test_scaling
2024-05-25 fix: typo
2024-05-25 On continu
2024-05-25 add: PAMI img & video
2024-05-25 test: responsive video
2024-05-25 enregistrement des modifs
2024-05-25 new: axes d'amélioration et images
2024-05-25 add: note about POI
2024-05-25 change: i love 4o
2024-05-26 Modif Robot et mise en route model viewer pami
2024-05-26 Revert mise en route Model viewer pami
2024-05-26 Ajout label Tests
2024-05-26 Add Robot snippet
2024-05-26 add RobotPoster
2024-05-26 add: code extract
2024-05-26 fix: ultrasonic ref
2024-05-26 add robot
2024-05-26 Rename Robot (3).gltf to Robot.gltf
2024-05-26 Ecrasement fichier corrompu
2024-05-26 changement vers technicals layout robot.md parceque je suis teubé
2024-05-26 Css modif on modelviewer
2024-05-26 tjr css
2024-05-26 Label move
2024-05-26 add: PAMI poster
2024-05-26 change: file struct
2024-05-26 Ecrasement placeholder poster (non final)
2024-05-26 add: PAMI journée des projets video
2024-05-27 Add vidéo robot
2024-05-27 Modif optimisation
2024-05-27 change: PAMI poster
2024-05-27 re-seize
2024-05-27 Modif Pami photo css
2024-05-27 With px
2024-05-27 typo erro
2024-05-27 seize test
2024-05-27 3d seize
2024-05-27 Rename Pami_v2.gltf to PAMI_v2.gltf
2024-05-27 test 3d files
2024-05-27 add poster for fix
2024-05-27 it doesnt work
2024-05-27 new: pollinisation page
2024-05-27 enregistrement modifs texte
2024-05-28 Modif Programmation
2024-05-29 enregistrement modif texte
2024-05-29 fix: fautes d'orthographe et clarté
2024-05-29 fix: more orthographe
2024-05-29 fix: even more orthographe
2024-05-30 fix: orthographe is no more
2024-05-30 Modif technicals pour bug fix
2024-05-30 enregistrement modif rr
2024-05-30 supression fichiez chassis a la demande de theo
2024-05-30 remove: invention de chatgpt sur la correction
2024-05-31 Modif matériaux et ajout image
2024-06-04 ajout prototypage
2024-06-04 change: official CDR logo color
2024-06-06 update conception+proto
2024-06-06 Reparation Kicad
2024-06-06 Ajout photo-robot
2024-06-06 ajout video assemblage
2024-06-06 maj-vod
2024-06-06 maj-2
2024-06-06 carter
2024-06-06 try again
2024-06-06 again and again
2024-06-06 add: reste de pollinisation PAMI
2024-06-06 test: model viewer fix?
2024-06-06 real fix
2024-06-06 it's so over
2024-06-06 test: div
2024-06-06 ajout des images/video de la pince, modifications du texte
2024-06-06 oupalumpa
2024-06-06 test alignement
2024-06-06 test changement de chemin
2024-06-06 fix ph ?
2024-06-06 essai video
2024-06-06 Text update p1
2024-06-06 testt
2024-06-06 oupss
2024-06-06 Reload model-viewer
2024-06-06 typo change
2024-06-06 commencement
2024-06-06 fix ligne
2024-06-06 loop video et ajout élément de jeu
2024-06-06 collage element de jeu
2024-06-06 2 eme essais
2024-06-06 test 3
2024-06-06 fix y 3d models
2024-06-06 test 4 reduire la taille des images
2024-06-06 reduction taille image plante
2024-06-06 test y inverse
2024-06-06 clear deprecated files
2024-06-06 ajout image
2024-06-06 Avancement V2
2024-06-06 mdr le 4
2024-06-07 proto
2024-06-07 up video
2024-06-07 Rename Premier_Start.webm
2024-06-07 Mise en forme video
2024-06-07 test fix
2024-06-07 modif taille image
2024-06-07 fix: children
2024-06-07 Pour un accent ?
2024-06-07 voilà
2024-06-07 Ajout pinout
2024-06-07 no way
2024-06-07 petit text en plus
2024-06-07 V4 add caratersistics
2024-06-07 chore: optimize jaw system with linear rail and servo motor
2024-06-07 test compress
2024-06-07 mise a jour fichier obti
2024-06-07 add new carteristics PCB
2024-06-08 correction fautes d'orthographes
2024-06-08 modif photo
2024-06-09 modif resultat et ajout vidéo / creation fichier barrilet
2024-06-09 chore: Update documentation for the barillet and pince mechanisms
2024-06-09 ajout de texte concernant le barillet
2024-06-09 ajout texte barrilet
2024-06-09 chore: Update documentation for the barillet mechanism and add video
2024-06-09 clean part 2
2024-06-09 adjuste
2024-06-10 Test_model-2
2024-06-10 fix: nav_order
2024-06-10 fix: syntax
2024-06-10 it works ??
2024-06-10 how??
2024-06-10 photo up
2024-06-10 plusiur maj
2024-06-10 chore: Update barillet documentation and remove unused images
2024-06-10 image fix ?
2024-06-10 J'ai trouver
2024-06-10 video implement
2024-06-10 fix video size
2024-06-10 a lot of bug fix
2024-06-10 ajust
2024-06-10 correction
2024-06-10 oups
2024-06-10 conclusion
2024-06-10 doc barillet
2024-06-10 changement de mise en forme
2024-06-10 fix name for the prototype N°2
2024-06-10 re structuration
2024-06-10 Correction des fautes d'orthographe par GPT
2024-06-10 ajout d'une phrase dans résultat
2024-06-11 add: PAMI source code
2024-06-11 revert
2024-06-11 revert: revert
2024-06-11 Add files
2024-06-11 ajout du lien
2024-06-11 Ajout lien OnShape et STEP du robot
2024-06-11 correction + ajout photo
2024-06-12 Maj ressources des projets (deso arthur)
2024-06-12 add: PAMI elec source
2024-06-12 image: webp conversion
2024-06-12 ajout bumper et roulements
2024-06-12 ajout lien
2024-06-12 fix: orthographe Conception PAMI
2024-06-12 Maj modifcation de recup et activation mermaid
2024-06-12 Ajout lien doc pour nema 17
2024-06-12 Ajout Submodule firmware + ajout datasheet tmc2209
2024-06-12 fix: actus n'a pas de children
2024-06-12 Ajout documentation servo moteurs
2024-06-12 Ajout petite partie batterie
2024-06-12 ajout photo+ correction
2024-06-12 Passage Chat GPT pour corriger les fautes
2024-06-12 ajout section barillet a la meca, ajout de lien
2024-06-12 correction plan meca
2024-06-12 ajout lien nema 17 dans la page barillet
2024-06-12 Passage de chat gpt sur V1 carte
2024-06-12 Passage de Chat gpt sur v2 carte
2024-06-12 Passage chatgpt sur V3 (Chatgpt ne sert qu'a ça, corriger mdr)
2024-06-12 Passage de chatgpt 4.0 sur v4
2024-06-12 Mise en forme
2024-06-12 image: webp conversion v2
2024-06-12 Harmonisation programmation avec mise en page programmation pami
2024-06-12 derniers changements de la part de dylan
2024-06-12 Vraiment... dernier changement... ces messages me coutent du temps précieux de sommeils
2024-06-12 correction faute
2024-06-12 Juste pour la blague de rendu a 23h59
2024-06-12 remove: unused images
2024-06-12 petit modif
